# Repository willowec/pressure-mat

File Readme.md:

# Pressure Mat Project

This git repository contains all the code developed for the Electrical and Computer Engineering Capstone project of Evan Desmond and Willow Cunningham at the University of Maine, Orono. 

## The Mat

The pressure sensing mat uses the intersections between rows and columns of copper tape separated by velostat to form resistive pressure sensors. The mat has 28 rows and 56 columns, for a total of 1568 sensors at a resolution of 1cm^2.

## The PCB

Schematics for the PCB are in ```/board_kicad``` A render of the pcb is shown below.

## The Code

Code for the project is split into two primary parts: embedded side and host side.

### Embedded Code

The code that the RPI Pico runs is in the ```/board_code``` directory. It is responsible for controlling the ADCs and shift registers on the PCB in order to read the pressure sensors in the mat, and transmitting the mat data over USB serial to the connected host computer.

### Host Code

The python program in ```/GUI```  is used to view data recorded and transmitted by the interface board.

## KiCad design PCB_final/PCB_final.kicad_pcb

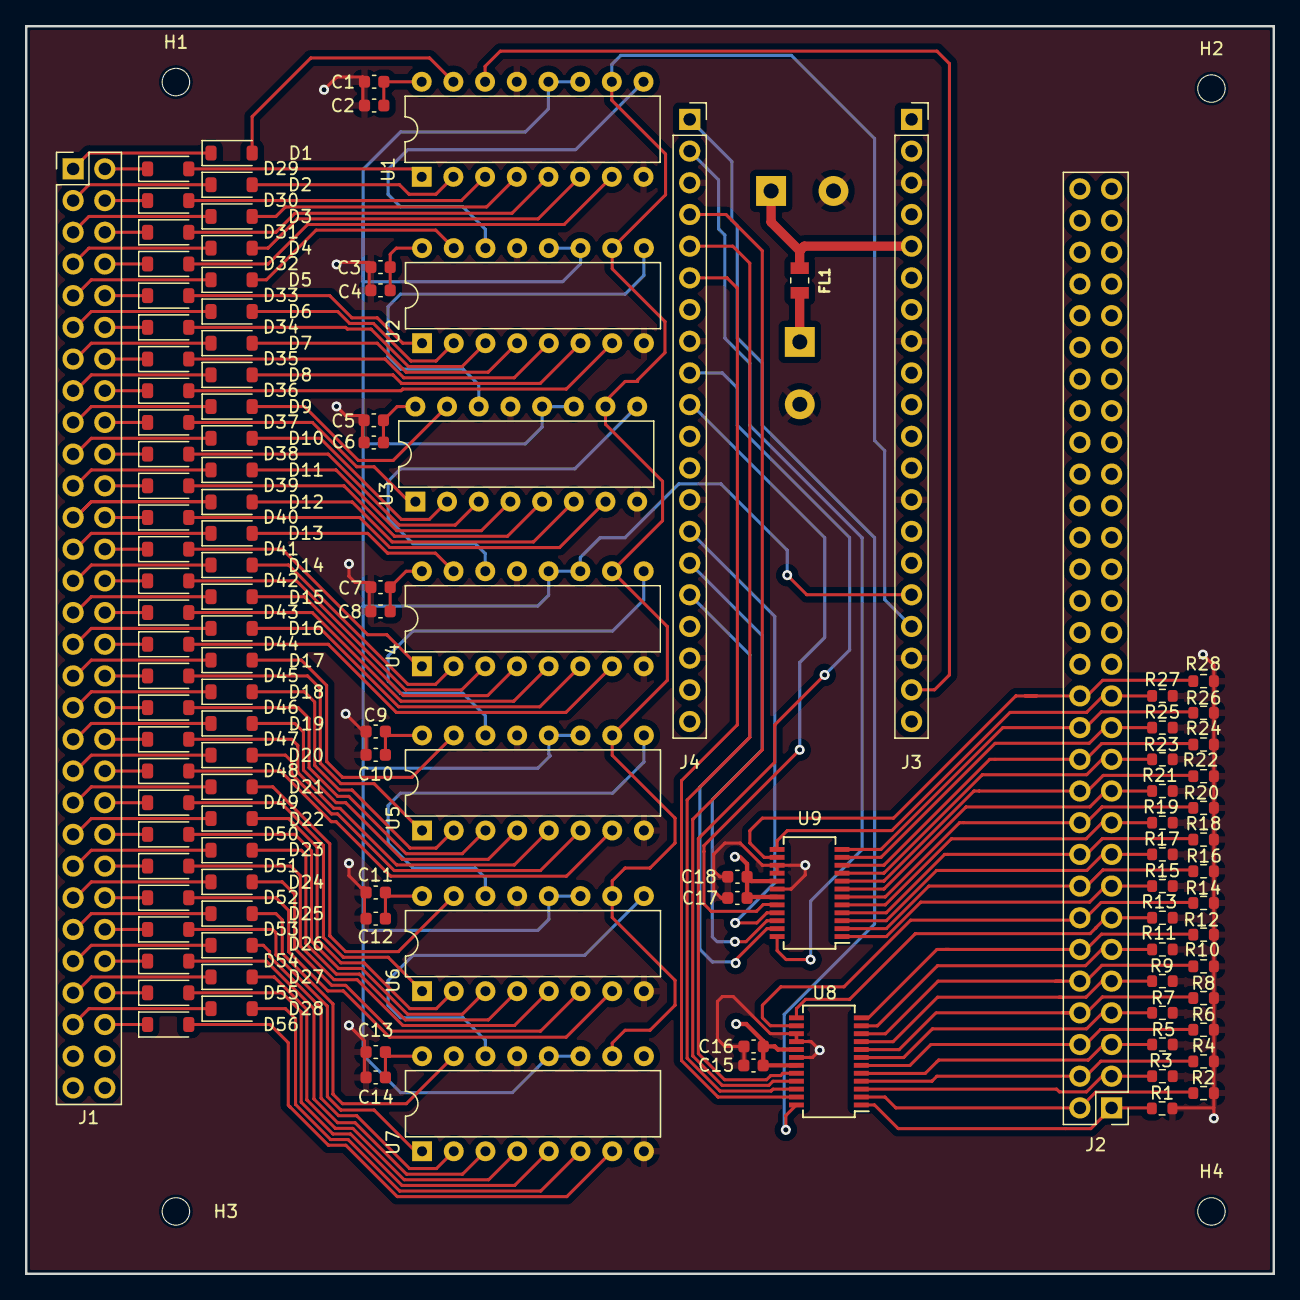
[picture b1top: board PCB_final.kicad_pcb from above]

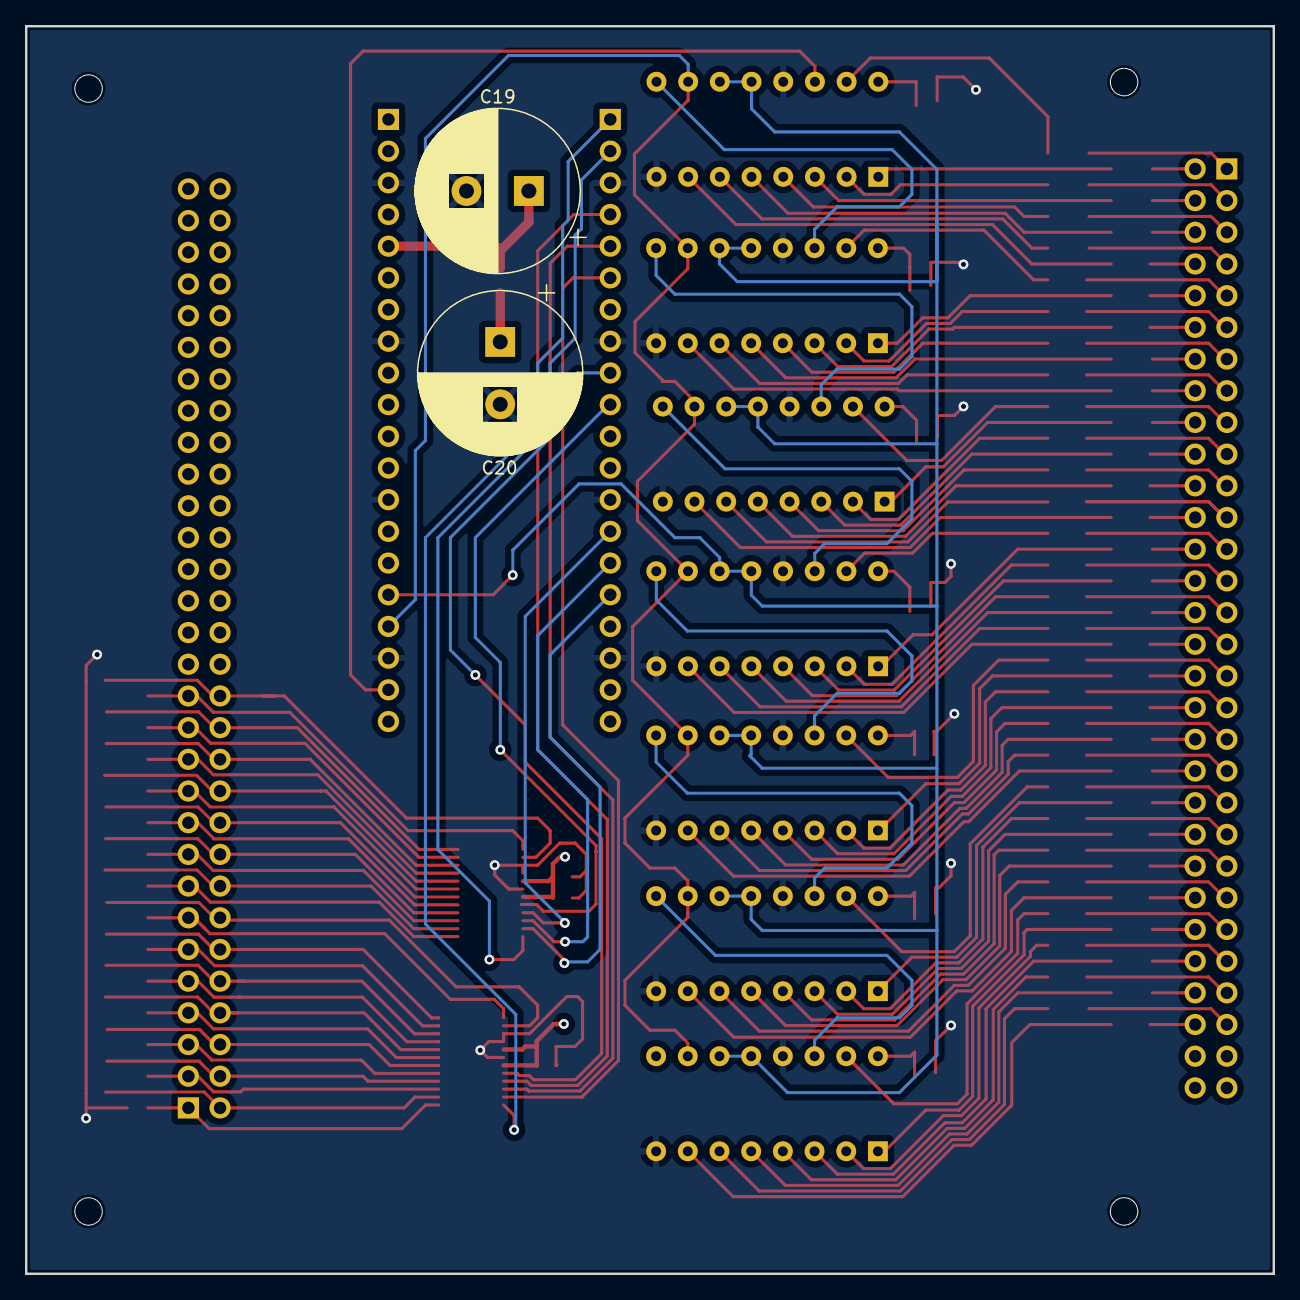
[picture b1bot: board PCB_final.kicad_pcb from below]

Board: 4 copper layers, 100.0 x 100.0 mm, 122 parts (2 on the bottom side), 162 nets.

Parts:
C1, C3, C5, C7, C9, C11, C13: 1uF; C_0603_1608Metric
C2, C4, C6, C8, C10, C12, C14: 0.1uF; C_0603_1608Metric
C15, C16, C17, C18: .1uF; C_0603_1608Metric
C19, C20: 4.7mF; CP_Radial_D13.0mm_P5.00mm
D1, D2, D3, D4, D5, D6, D7, D8, D9, D10, D11, D12, D13, D14, D15, D16, D17, D18, D19, D20, D21, D22, D23, D24, D25, D26, D27, D28, D29, D30, D31, D32, D33, D34, D35, D36, D37, D38, D39, D40, D41, D42, D43, D44, D45, D46, D47, D48, D49, D50, D51, D52, D53, D54, D55, D56: MMSD4148; D_SOD-123
FL1: BLM21BD272SN1L; BEADC2012X145N
H1, H2, H3, H4: MountingHole; MountingHole_2.2mm_M2
J1: 02x30_Shift_Register_Connector; PinHeader_2x30_P2.54mm_Vertical
J2: 02x30_ADC_Connector; PinHeader_2x30_P2.54mm_Vertical
J3: PicoPinSocketB; PinSocket_1x20_P2.54mm_Vertical
J4: PicoPinSocketA; PinSocket_1x20_P2.54mm_Vertical
R1, R2, R3, R4, R5, R6, R7, R8, R9, R10, R11, R12, R13, R14, R15, R16, R17, R18, R19, R20, R21, R22, R23, R24, R25, R26, R27, R28: 100k; R_0603_1608Metric
U1, U2, U3, U4, U5, U6, U7: 74HC595; DIP-16_W7.62mm
U8, U9: MAX11643EEG; SSOP-24_3.9x8.7mm_P0.635mm

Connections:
3V3_Pico: C19.1, FL1.1, J3.5
+3V3: C1.1, C2.1, C3.1, C4.1, C5.1, C6.1, C7.1, C8.1, C9.1, C10.1, C11.1, C12.1, C13.1, C14.1, C15.1, C16.1, C17.1, C18.1, C20.1, FL1.2, U1.16 (VCC), U2.16 (VCC), U3.16 (VCC), U4.16 (VCC), U5.16 (VCC), U6.16 (VCC), U7.16 (VCC), U8.17 (REF), U8.19 (VDD), U9.17 (REF), U9.19 (VDD)
/Interface Board/ADC1_EOC: J4.1, U8.24 (EOC)
/Interface Board/ADC2_EOC: J4.2, U9.24 (EOC)
/Interface Board/ADC_IN1: J2.1, R1.1, U8.1 (AIN0)
/Interface Board/ADC_IN2: J2.2, R2.1, U8.2 (AIN1)
/Interface Board/ADC_IN3: J2.3, R3.1, U8.3 (AIN2)
/Interface Board/ADC_IN4: J2.4, R4.1, U8.4 (AIN3)
/Interface Board/ADC_IN5: J2.5, R5.1, U8.5 (AIN4)
/Interface Board/ADC_IN6: J2.6, R6.1, U8.6 (AIN5)
/Interface Board/ADC_IN7: J2.7, R7.1, U8.7 (AIN6)
/Interface Board/ADC_IN8: J2.8, R8.1, U8.8 (AIN7)
/Interface Board/ADC_IN9: J2.9, R9.1, U8.9 (AIN8)
/Interface Board/ADC_IN10: J2.10, R10.1, U8.10 (AIN9)
/Interface Board/ADC_IN11: J2.11, R11.1, U8.11 (AIN10)
/Interface Board/ADC_IN12: J2.12, R12.1, U8.12 (AIN11)
/Interface Board/ADC_IN13: J2.13, R13.1, U8.13 (AIN12)
/Interface Board/ADC_IN14: J2.14, R14.1, U8.14 (AIN13)
/Interface Board/ADC_IN15: J2.15, R15.1, U9.1 (AIN0)
/Interface Board/ADC_IN16: J2.16, R16.1, U9.2 (AIN1)
/Interface Board/ADC_IN17: J2.17, R17.1, U9.3 (AIN2)
/Interface Board/ADC_IN18: J2.18, R18.1, U9.4 (AIN3)
/Interface Board/ADC_IN19: J2.19, R19.1, U9.5 (AIN4)
/Interface Board/ADC_IN20: J2.20, R20.1, U9.6 (AIN5)
/Interface Board/ADC_IN21: J2.21, R21.1, U9.7 (AIN6)
/Interface Board/ADC_IN22: J2.22, R22.1, U9.8 (AIN7)
/Interface Board/ADC_IN23: J2.23, R23.1, U9.9 (AIN8)
/Interface Board/ADC_IN24: J2.24, R24.1, U9.10 (AIN9)
/Interface Board/ADC_IN25: J2.25, R25.1, U9.11 (AIN10)
/Interface Board/ADC_IN26: J2.26, R26.1, U9.12 (AIN11)
/Interface Board/ADC_IN27: J2.27, R27.1, U9.13 (AIN12)
/Interface Board/ADC_IN28: J2.28, R28.1, U9.14 (AIN13)
/Interface Board/CS0: J4.9, U8.20 (CS)
/Interface Board/CS1: J4.10, U9.20 (CS)
/Interface Board/SER5: U4.9 (QH'), U5.14 (SER)
/Interface Board/SH_CLK: J3.16, U1.11 (SRCLK), U1.12 (RCLK), U2.11 (SRCLK), U2.12 (RCLK), U3.11 (SRCLK), U3.12 (RCLK), U4.11 (SRCLK), U4.12 (RCLK), U5.11 (SRCLK), U5.12 (RCLK), U6.11 (SRCLK), U6.12 (RCLK), U7.11 (SRCLK), U7.12 (RCLK)
/Interface Board/SH_CLR: J3.17, U1.10 (~SRCLR), U2.10 (~SRCLR), U3.10 (~SRCLR), U4.10 (~SRCLR), U5.10 (~SRCLR), U6.10 (~SRCLR), U7.10 (~SRCLR)
/Interface Board/SH_SERIN: J3.19, U1.14 (SER)
/Interface Board/SOUT1: D1.2 (A), U1.15 (QA)
/Interface Board/SOUT2: D29.2 (A), U1.1 (QB)
/Interface Board/SOUT3: D2.2 (A), U1.2 (QC)
/Interface Board/SOUT4: D30.2 (A), U1.3 (QD)
/Interface Board/SOUT5: D3.2 (A), U1.4 (QE)
/Interface Board/SOUT6: D31.2 (A), U1.5 (QF)
/Interface Board/SOUT7: D4.2 (A), U1.6 (QG)
/Interface Board/SOUT8: D32.2 (A), U1.7 (QH)
/Interface Board/SOUT9: D5.2 (A), U2.15 (QA)
/Interface Board/SOUT10: D33.2 (A), U2.1 (QB)
/Interface Board/SOUT11: D6.2 (A), U2.2 (QC)
/Interface Board/SOUT12: D34.2 (A), U2.3 (QD)
/Interface Board/SOUT13: D7.2 (A), U2.4 (QE)
/Interface Board/SOUT14: D35.2 (A), U2.5 (QF)
/Interface Board/SOUT15: D8.2 (A), U2.6 (QG)
/Interface Board/SOUT16: D36.2 (A), U2.7 (QH)
/Interface Board/SOUT17: D9.2 (A), U3.15 (QA)
/Interface Board/SOUT18: D37.2 (A), U3.1 (QB)
/Interface Board/SOUT19: D10.2 (A), U3.2 (QC)
/Interface Board/SOUT20: D38.2 (A), U3.3 (QD)
/Interface Board/SOUT21: D11.2 (A), U3.4 (QE)
/Interface Board/SOUT22: D39.2 (A), U3.5 (QF)
/Interface Board/SOUT23: D12.2 (A), U3.6 (QG)
/Interface Board/SOUT24: D40.2 (A), U3.7 (QH)
/Interface Board/SOUT25: D13.2 (A), U4.15 (QA)
/Interface Board/SOUT26: D41.2 (A), U4.1 (QB)
/Interface Board/SOUT27: D14.2 (A), U4.2 (QC)
/Interface Board/SOUT28: D42.2 (A), U4.3 (QD)
/Interface Board/SOUT29: D15.2 (A), U4.4 (QE)
/Interface Board/SOUT30: D43.2 (A), U4.5 (QF)
/Interface Board/SOUT31: D16.2 (A), U4.6 (QG)
/Interface Board/SOUT32: D44.2 (A), U4.7 (QH)
/Interface Board/SOUT33: D17.2 (A), U5.15 (QA)
/Interface Board/SOUT34: D45.2 (A), U5.1 (QB)
/Interface Board/SOUT35: D18.2 (A), U5.2 (QC)
/Interface Board/SOUT36: D46.2 (A), U5.3 (QD)
/Interface Board/SOUT37: D19.2 (A), U5.4 (QE)
/Interface Board/SOUT38: D47.2 (A), U5.5 (QF)
/Interface Board/SOUT39: D20.2 (A), U5.6 (QG)
/Interface Board/SOUT40: D48.2 (A), U5.7 (QH)
/Interface Board/SOUT41: D21.2 (A), U6.15 (QA)
/Interface Board/SOUT42: D49.2 (A), U6.1 (QB)
/Interface Board/SOUT43: D22.2 (A), U6.2 (QC)
/Interface Board/SOUT44: D50.2 (A), U6.3 (QD)
/Interface Board/SOUT45: D23.2 (A), U6.4 (QE)
/Interface Board/SOUT46: D51.2 (A), U6.5 (QF)
/Interface Board/SOUT47: D24.2 (A), U6.6 (QG)
/Interface Board/SOUT48: D52.2 (A), U6.7 (QH)
/Interface Board/SOUT49: D25.2 (A), U7.15 (QA)
/Interface Board/SOUT50: D53.2 (A), U7.1 (QB)
/Interface Board/SOUT51: D26.2 (A), U7.2 (QC)
/Interface Board/SOUT52: D54.2 (A), U7.3 (QD)
/Interface Board/SOUT53: D27.2 (A), U7.4 (QE)
/Interface Board/SOUT54: D55.2 (A), U7.5 (QF)
/Interface Board/SOUT55: D28.2 (A), U7.6 (QG)
/Interface Board/SOUT56: D56.2 (A), U7.7 (QH)
/Interface Board/SPI0_RX: J4.6, U8.23 (DOUT)
/Interface Board/SPI0_SCK: J4.4, U8.21 (SCLK)
/Interface Board/SPI0_TX: J4.5, U8.22 (DIN)
/Interface Board/SPI1_RX: J4.16, U9.23 (DOUT)
/Interface Board/SPI1_SCK: J4.14, U9.21 (SCLK)
/Interface Board/SPI1_TX: J4.15, U9.22 (DIN)
GND: C1.2, C2.2, C3.2, C4.2, C5.2, C6.2, C7.2, C8.2, C9.2, C10.2, C11.2, C12.2, C13.2, C14.2, C15.2, C16.2, C17.2, C18.2, C19.2, C20.2, J3.3, J3.8, J3.13, J3.18, J4.3, J4.8, J4.13, J4.18, R1.2, R2.2, R3.2, R4.2, R5.2, R6.2, R7.2, R8.2, R9.2, R10.2, R11.2, R12.2, R13.2, R14.2, R15.2, R16.2, R17.2, R18.2, R19.2, R20.2, R21.2, R22.2, R23.2, R24.2, R25.2, R26.2, R27.2, R28.2, U1.8 (GND), U1.13 (~OE), U2.8 (GND), U2.13 (~OE), U3.8 (GND), U3.13 (~OE), U4.8 (GND), U4.13 (~OE), U5.8 (GND), U5.13 (~OE), U6.8 (GND), U6.13 (~OE), U7.8 (GND), U7.13 (~OE), U8.15 (AIN14), U8.16 (AIN15), U8.18 (GND), U9.15 (AIN14), U9.16 (AIN15), U9.18 (GND)
unnamed: D1.1 (K), J1.1
unnamed: D2.1 (K), J1.3
unnamed: D3.1 (K), J1.5
unnamed: D4.1 (K), J1.7
unnamed: D5.1 (K), J1.9
unnamed: D6.1 (K), J1.11
unnamed: D7.1 (K), J1.13
unnamed: D8.1 (K), J1.15
unnamed: D9.1 (K), J1.17
unnamed: D10.1 (K), J1.19
unnamed: D11.1 (K), J1.21
unnamed: D12.1 (K), J1.23
unnamed: D13.1 (K), J1.25
unnamed: D14.1 (K), J1.27
unnamed: D15.1 (K), J1.29
unnamed: D16.1 (K), J1.31
unnamed: D17.1 (K), J1.33
unnamed: D18.1 (K), J1.35
unnamed: D19.1 (K), J1.37
unnamed: D20.1 (K), J1.39
unnamed: D21.1 (K), J1.41
unnamed: D22.1 (K), J1.43
unnamed: D23.1 (K), J1.45
unnamed: D24.1 (K), J1.47
unnamed: D25.1 (K), J1.49
unnamed: D26.1 (K), J1.51
unnamed: D27.1 (K), J1.53
unnamed: D28.1 (K), J1.55
unnamed: D29.1 (K), J1.2
unnamed: D30.1 (K), J1.4
unnamed: D31.1 (K), J1.6
unnamed: D32.1 (K), J1.8
unnamed: D33.1 (K), J1.10
unnamed: D34.1 (K), J1.12
unnamed: D35.1 (K), J1.14
unnamed: D36.1 (K), J1.16
unnamed: D37.1 (K), J1.18
unnamed: D38.1 (K), J1.20
unnamed: D39.1 (K), J1.22
unnamed: D40.1 (K), J1.24
unnamed: D41.1 (K), J1.26
unnamed: D42.1 (K), J1.28
unnamed: D43.1 (K), J1.30
unnamed: D44.1 (K), J1.32
unnamed: D45.1 (K), J1.34
unnamed: D46.1 (K), J1.36
unnamed: D47.1 (K), J1.38
unnamed: D48.1 (K), J1.40
unnamed: D49.1 (K), J1.42
unnamed: D50.1 (K), J1.44
unnamed: D51.1 (K), J1.46
unnamed: D52.1 (K), J1.48
unnamed: D53.1 (K), J1.50
unnamed: D54.1 (K), J1.52
unnamed: D55.1 (K), J1.54
unnamed: D56.1 (K), J1.56
unnamed: U1.9 (QH'), U2.14 (SER)
unnamed: U2.9 (QH'), U3.14 (SER)
unnamed: U3.9 (QH'), U4.14 (SER)
unnamed: U5.9 (QH'), U6.14 (SER)
unnamed: U6.9 (QH'), U7.14 (SER)

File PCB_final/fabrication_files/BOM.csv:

"Id";"Designator";"Footprint";"Quantity";"Designation";"Supplier and ref";
1;"C8,C14,C10,C2,C17,C4,C12,C6";"C_0603_1608Metric";8;"0.1uF";;;
2;"D35,D36,D2,D54,D18,D45,D25,D15,D11,D31,D55,D10,D30,D43,D56,D19,D9,D8,D44,D42,D32,D5,D28,D47,D6,D14,D21,D34,D52,D53,D3,D22,D17,D4,D40,D46,D29,D26,D48,D41,D49,D12,D37,D38,D23,D20,D7,D39,D51,D13,D27,D16,D33,D50,D24,D1";"D_SOD-123";56;"MMSD4148";;;
3;"R3,R13,R18,R27,R20,R25,R9,R26,R24,R11,R4,R14,R28,R2,R21,R10,R12,R5,R7,R17,R16,R23,R1,R8,R19,R15,R29,R22,R6";"R_0603_1608Metric";29;"100k";;;
4;"C9,C7,C5,C3,C11,C13,C1";"C_0603_1608Metric";7;"1uF";;;
5;"U2,U6,U3,U7,U4,U1,U5";"DIP-16_W7.62mm";7;"74HC595";;;
6;"J5";"PinSocket_1x20_P2.54mm_Vertical";1;"PicoPinSocketB";;;
7;"C16,C15";"C_0603_1608Metric";2;".1uF";;;
8;"J1";"PinHeader_2x30_P2.54mm_Vertical";1;"02x30_Shift_Register_Connector";;;
9;"U9,U8";"SSOP-24_3.9x8.7mm_P0.635mm";2;"MAX11643EEG";;;
10;"J2";"PinHeader_2x30_P2.54mm_Vertical";1;"02x30_ADC_Connector";;;
11;"U10";"SOT-23-5";1;"LM321";;;
12;"J6";"PinSocket_1x20_P2.54mm_Vertical";1;"PicoPinSocketA";;;

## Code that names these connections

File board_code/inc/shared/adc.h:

/*
Header file responsible for communicating via spi to the two ADC's of the project
This code is written assuming that the ADC's are MAX11643 chips
*/
#ifndef ADC_HEADER
#define ADC_HEADER

#include <stdint.h>
#include <stdbool.h>

#include "hardware/spi.h"

#define ADC_RESPONSE_LENGTH 28
#define CHANNELS_PER_ADC    14  // 14 pins of the adc's each are connected to the mat

#define SPI0_SCK_PIN        2
#define SPI0_TX_PIN         3
#define SPI0_RX_PIN         4

#define SPI1_SCK_PIN        10
#define SPI1_TX_PIN         11
#define SPI1_RX_PIN         12

#define SPI_CLOCKSPEED      2000000 // 2MHz
#define CS_SELECT           0
#define CS_DESELECT         1

#define ADC1_EOC_PIN        0
#define ADC2_EOC_PIN        1
#define ADC1_CS_PIN         6
#define ADC2_CS_PIN         7


struct adc_inst {
    uint8_t cs_pin;
    uint8_t eoc_pin;
    spi_inst_t *spi_channel;
};

/*
Initializes the spi channel used to talk to the ADCs, and calls initialze_adc() for both of them
Set dual_channel=true if using on board version 2 in order for each adc to have its own SPI channel
*/
void initialize_adcs(struct adc_inst *adc1, struct adc_inst *adc2, bool dual_channel);

/*
Initializes an ADC (sets setup register values, etc)
*/
void initialize_adc(struct adc_inst *adc);

/*
Gets samples from channel 0 to CHANNELS_PER_ADC of the adc_inst 'adc' and writes their values to 'out_vals'
*/
void get_adc_values(struct adc_inst* adc, uint8_t *out_vals);

/*
Wraps spi_write_blocking to communcicate with an adc
*/
void adc_write_blocking(struct adc_inst* adc, uint8_t *src, size_t len);

/*
Wraps spi_read_blocking to communcicate with an adc
*/
void adc_read_blocking(struct adc_inst* adc, uint8_t repeated_tx_data, uint8_t *dst, size_t len);

/*
Takes the raw response to a conversion request from the ADC and cleans it up to be a simple array of readings
*/
void cleanup_adc_response(uint8_t *resp, uint8_t *out_values);

#endif

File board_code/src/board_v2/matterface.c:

/*
Mat interface code for V2 of the PMI software
*/

#include <stdio.h>
#include <stdbool.h>

#include "hardware/gpio.h"
#include "pico/stdlib.h"

#include "matterface.h"
#include "transmitter.h"

#define LED_PIN         25

// For the interrupt-based mat read to work, some global variables are required
queue_t *mat_queue_ptr;
uint8_t row_data[ROW_WIDTH] = {9};  // intialize the row data with a clearly invalid data
struct queueItem row_item;

int column;
struct adc_inst *adc1_instance;
struct adc_inst *adc2_instance;
bool waiting_for_adc1;
bool waiting_for_adc2;
volatile bool reading_mat;  // must be volatile for global changes to be recognized


void initialize_shreg_pins()
{
    gpio_init(SH_CLK_PIN);
    gpio_set_dir(SH_CLK_PIN, GPIO_OUT);

    gpio_init(SH_CLR_PIN);
    gpio_set_dir(SH_CLR_PIN, GPIO_OUT);

    gpio_init(SH_SERIN_PIN);
    gpio_set_dir(SH_SERIN_PIN, GPIO_OUT);

    gpio_init(SH_SEROUT_PIN);
    gpio_set_dir(SH_SEROUT_PIN, GPIO_IN);

    // make sure the shift registers are initialized to zero
    clear_shreg();
}

void shift_shreg(int inval)
{
    // write the serial input value to the shift registers
    gpio_put(SH_SERIN_PIN, inval);

    // clock the shift registers once
    gpio_put(SH_CLK_PIN, 1);
    busy_wait_us_32(SHREG_GPIO_SLEEP_US);
    gpio_put(SH_CLK_PIN, 0);
}

void clear_shreg()
{
    // flicker the clear pin to reset the shift registers
    gpio_put(SH_CLR_PIN, 0);
    busy_wait_us_32(SHREG_GPIO_SLEEP_US);
    gpio_put(SH_CLR_PIN, 1);
}

/*
Callback function that is triggered by either of the ADC's EOC pins going low.
*/
void EOC_callback(uint gpio, uint32_t events) 
{
    if (!reading_mat) {
        return;   // do not process events if not reading the mat
    } 

    /* 
     * An EOC pin just went low! Let's handle this
     * 1. for the EOC pin:
     *  1.1. read results from the corresponding ADC
     *  1.2. transmit the results over the queue to core 1
     *  1.3. set waiting_for_adcX to false
     * 2. if waiting_for_adc1 and waiting_for_adc2 are both false:
     *  2.1. shift the shregs
     *  2.2. inc the column counter
     *  2.3. request a new conversion from both ADCs
     */

    int i;
    bool ret;

    // define a temp array for storing and processing the values returned from the ADCs
    uint8_t *resp = (uint8_t *)malloc(ADC_RESPONSE_LENGTH);

    // step 1
    if (gpio == ADC1_EOC_PIN) {
        // handle ADC1 results
        waiting_for_adc1 = false;

        // read the conversion results
        adc_read_blocking(adc1_instance, 0, resp, ADC_RESPONSE_LENGTH);
        cleanup_adc_response(resp, row_data);
    }
    else if (gpio == ADC2_EOC_PIN) {
        // handle ADC2 results
        waiting_for_adc2 = false;

        // read the conversion results
        adc_read_blocking(adc2_instance, 0, resp, ADC_RESPONSE_LENGTH);
        cleanup_adc_response(resp, row_data + CHANNELS_PER_ADC);
    }

    // step 2
    if ((!waiting_for_adc1) && (!waiting_for_adc2)) {
        // Both adc's have been read! push the row data onto the queue
        row_item.row_data = row_data;

        queue_add_blocking(mat_queue_ptr, &row_item);

        // set up the shift registers for the next adc sample requests
        shift_shreg(0);
        column++;

        // if column == COL_HEIGHT, then we are finished and should requet any more readings
        if (column == COL_HEIGHT) {
            reading_mat = false;
        }
        else {
            // delay before the next set of ADC requests
            busy_wait_us_32(ADC_READ_SLEEP_US); // cannot call sleep_us within interrupt handlers, busy wait instead

            // request all channels from both ADCs
            waiting_for_adc1 = true;
            waiting_for_adc2 = true;
            uint8_t conv_req = 0b10000000 | ((CHANNELS_PER_ADC - 1) << 3);  // conversion request command
            adc_write_blocking(adc1_instance, &conv_req, 1);
            adc_write_blocking(adc2_instance, &conv_req, 1);
        }
    }

    free(resp);
}

void initialize_EOC_interrupts() 
{
    reading_mat = false;

    // set up both EOC pins to trigger a callback on the falling edge of the EOC lines (falling edge occurs when the ADC completes its read)   
    gpio_set_irq_enabled_with_callback(ADC1_EOC_PIN, GPIO_IRQ_EDGE_FALL, true, &EOC_callback);
    gpio_set_irq_enabled(ADC2_EOC_PIN, GPIO_IRQ_EDGE_FALL, true);
}

void read_mat(queue_t *mat_queue, struct adc_inst *adc1, struct adc_inst *adc2)
{
    // do not start reading the mat if a read is already happening
    if (reading_mat) return;

    // Throttle the mat reading rate based on the CMake build variable
    sleep_ms(THROTTLE_SLEEP_MS);

    // start with a one in the shregs
    shift_shreg(1); // shift in a one
    shift_shreg(0); // move the one to the output line

    // set up the global variables for interrupt handling
    mat_queue_ptr = mat_queue;
    adc1_instance = adc1;
    adc2_instance = adc2;
    
    waiting_for_adc1 = false;
    waiting_for_adc2 = false;

    column = 0;

    // indicate that a read is currently happening
    reading_mat = true;

    // send the first ADC read requests to get things started
    // write a conversion request in scan mode 00 for channels 0 -> (CHANNELS_PER_ADC - 1), for CHANNELS_PER_ADC total channels
    uint8_t conv_req = 0b10000000 | ((CHANNELS_PER_ADC - 1) << 3);
    adc_write_blocking(adc1_instance, &conv_req, 1);
    adc_write_blocking(adc2_instance, &conv_req, 1);

    // now just busy-wait until the mat is completely read.
    int i = 0;
    while(reading_mat) 
        i++;
    
    return;
}


void prettyprint_mat(uint8_t *mat)
{
    int i;
    for (i = 0; i < MAT_SIZE; i++)
    {
        if ((i % ROW_WIDTH) == 0) {
            printf("\b  \n");   // on every row, clear the trailing comma and add a newline
        }

        printf("%02x, ", mat[i]);
    }

    printf("\b  \n");
}

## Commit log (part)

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2023-05-16 Stopped tracking png
2023-05-17 Sampling code has artefacts alternating every read. investigationg
2023-05-25 minor tweaks
2023-05-28 Added note about the diodes
2023-08-30 Replaced incorrect alt text
2023-09-04 Added 4/7 shift registers and connected them to connection block, I believe this could be improved with bus lines
2023-09-05 Added 7/7 shift registers with fully connected inputs and outputs, need to look into necesity of decoupling capacitor on GND
2023-09-05 ignoring irrelevant kicad stuff
2023-09-05 removed irrelevant kicad stuff
2023-09-05 Changed all shift registers to be on the same SCLK, RCLK and OE. Also connected shift register 4 to 5 using node names
2023-09-06 used nodes to reconnect ADC's to new connectors and added voltage dividers to all ADC inputs
2023-09-06 added diodes to between all shift register outputs and the connector
2023-09-07 ignoring info cache
2023-09-07 added decouple caps for the ADCs
2023-09-11 Created new folder for PCB with RP2040 included
2023-09-11 Separated RP2040 and interface board components into multiple sheets
2023-09-12 changed diodes to the correct surface mount diodes we will be using on the final pcb
2023-09-12 beautified shift registers by putting decoupling capacitors as external elements and put in actual capacitor values
2023-09-15 Added guide for programming the pico
2023-09-16 ignoring builds
2023-09-16 began stub of python version of the dummy adc
2023-09-16 Added short explanation of the c_example
2023-09-16 began multicore/spi example
2023-09-17 Added C example of an spi client running on core 1 and an spi controller running on core 2, talking to each other
2023-09-17 typo fix
2023-09-17 Began C implementation
2023-09-18 issue seems to be fixed
2023-09-19 Moved old pcb to prototypes
2023-09-19 Added active-low pass filter for power supply to schematic. Need to decide which OP AMP, resistor, and capacitor to use.
2023-09-19 Added clock connection for ADCs
2023-09-19 Selected values for low-pass filter: C=0.1uF, R=500ohm, Fc=3.2kHz. Still need to select op amp, but we can probably go with whatever is readily available in parts cabinent
2023-09-19 noconnected relevant pins
2023-09-19 Added clock pin connections
2023-09-20 Updated op amp and added rpi pico to schematic
2023-09-21 Added load past session button
2023-09-21 Created a sessions folder in GUI to hold past sessions. Also added a folder of a 'past session' with 3 images to test GUI with
2023-09-21 Connected all pins to the pico
2023-09-22 Changed images to be 56 wide by 28 tall. Beautified GUI. And got image scaling to work so the foot pressure images are displayed at 10x
2023-09-22 Began embedded code
2023-09-25 Changed to use only one spi channe.
2023-09-25 Added file selector to 'load past session' button, does not properly update image yet
2023-09-25 'Load past session' button now updates image on page but is not scaled correctly yet
2023-09-25 began adc code
2023-09-26 Added spi wrapper functions to adc.h
2023-09-26 Added the get_next_img() function that will get an image with +/- 1 index to the current image. Applied this function to image navigator buttons to get them functioning. Still need to add protections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
2023-09-26 Added comments to get_next_image(), load_past_img_next(), and load_past_img_prev()
2023-09-26 Attempts to read from adc
2023-09-27 SPI comms with the fake adc's most of the way there, although the response is never being sent
2023-09-27 Added session class to be initialized when the start session button is clicked. Not tested yet and only creates a folder with the current date and time right now
2023-09-28 Added footprints to the ADCS
2023-09-28 upon initialization the session class now creates a folder named by the current date and time in the /sessions directory. folder name is in the format of yy_mm_dd_THH_MM_SS
2023-10-01 Added footprints to all components
2023-10-01 nearly finished with pcb routing
2023-10-02 fully connected, thermal pad errors
2023-10-02 fixed board edge
2023-10-02 Changed Reciever class so that connecting to the board is its own function. Modified the connect_board() function in the MainWindow class so that it updates the reciever with the input port and baud 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
2023-10-03 Started creating image saving to the correct index within the reciever class
2023-10-07 Began mat interface code. Code-side ADC issues are all fixed.
2023-10-08 Now interfacing and prettyprinting the mat
2023-10-08 Attempting to see difference between weighted and unweighted mat
2023-10-11 Added PWR and GND planes to PCB
2023-10-12 PCB complete and redesigned w 4 layers. Passes desgin rule checker except for most of the silk screens. Schematic updated to connect adc unused pins to ground and beatified schematic
2023-10-12 PCB silkscreen moved to stop warnings. Still getting a lot of seemingly unimportant errors from silkscreen. Updated design constraints to match manufacturer capabilities. Fixed a trace that was clipp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
2023-10-12 Created directory for PCB fabrication files and populated it
2023-10-13 Deleted manual PCB fab files and switched to JLCPCB plugin fab file output. Modified BOM and Positions files, removing the shift registers and pico pin headers. I suggest we also remove ribbon cable 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
2023-10-13 slight formatting
2023-10-15 Many caps on schematic were labeled c1 and c2 incorrectly. Swapped power supply filter to Pi filter, but with no value for L yet.
2023-10-15 Fixed tpe hinting issue that prevented startup
2023-10-15 Moved communcation with the mat to its own module. Many issues outstanding
2023-10-16 most basic possible transmitting
2023-10-16 Added MCP6001 PCB
2023-10-16 Board now waits for message to start sampling
2023-10-16 Found naming errors with schematic and a few traces in PCB that weren't connected correctly. PCB now passes DRC with only a few warnings about silkscreen
2023-10-16 Comms argely working. Issue where board fails early into first mat read
2023-10-17 Removed filter from schematic and PCB. Adjusted tracings on PCB and schematic for ADC inputs so that each ADC has 14 inputs
2023-10-17 Removed old PCB production files and added new ones. Removed components from BOM and positions files that we are soldering ourselves
2023-10-17 debugging in progress
2023-10-19 board communcations are still flawed. Current im_array conversion is correct. Need to investigate fwrite
2023-10-19 Chnaged comms to use hexadecimal. Issue now is that it seems to only be transmitting up a value 0-16
2023-10-19 prettyprinting the array shows that the problem might be with tthe saving of the image
2023-10-23 Fixed a lot of issues with the data transmission to the GUI, but data is still checkerboarded at source
2023-10-24 Finally figured out ADC comms once and for all
2023-10-24 Using new info, fixed comms
2023-10-24 ignoring oycache
2023-10-24 Updated filter's ferrite bead and capacitors on schematic and PCB. Power supply filter now fully integrated
2023-10-30 Added note on pcb to indicate direction pico faces
2023-10-30 Updated clock rate
2023-10-31 temp fix eliminating ADC1 due to hardware failure
2023-11-02 Initial structure layout
2023-11-03 A historical moment. Genuinely worked the first try
2023-11-07 Multicore example now includes built-in queue
2023-11-07 Updated kicad PCB to use both SPI channels of the RPI Pico
2023-11-07 Changed inductor silkscreen to meet production constraints
2023-11-07 Made matterface talk to both ADC's again
2023-11-07 Fixed issue where first column of mat would be skipped by shregs
2023-11-07 Moved conversion of mat reading from array to np.ndarray from save_image() to run()
2023-11-07 Began linking calibration logiv to GUI
2023-11-08 Updated PCB for quality of life. Increased size to 100mmx100mm. Rotated pico 180 degrees. Aligned ribbon cable connectors. Moved silk screens to better locations. Moved mounting holes to better locat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
2023-11-08 Restored normal functions, mat seems to be working after it got a good night's sleep?
2023-11-08 UI fully finished, actual curbe calculations needs a lot of work
2023-11-09 Ignoring calibrator unless it is calibrated
2023-11-09 Moved silkscreen text to better locations
2023-11-09 Added a test for extreme order polynomial
2023-11-09 Made calibration select a lower polyfit degree if not enough samples are passed
2023-11-14 changed sample rate to over 1Hz
2023-11-14 Added default calibration values. Calibrator is still not playing nice
2023-11-14 disabled saving of default cal
2023-11-14 Added data plotting file
2023-11-15 Now plotting calibration curves
2023-11-16 Calculating calibration curves via scipy semi-implemented
2023-11-16 ZERO CURVE FIT FAILURES!!!!!!!
2023-11-16 Added step size plot
2023-11-16 plot_readings now calculates percentage error at max step size
2023-11-17 Removed obsolete calibration buttons
2023-11-17 Removed outdated image code
2023-11-20 Added average cal curves
2023-11-20 Added % error calculations to the stats box
2023-11-21 Added slider to GUI. Removed nav buttons. Still need to flesh out slider
2023-11-27 minor edits
2023-11-27 Added a second build target for board v2 and a print_info command
2023-11-28 Started trying to use interrupts, but program unable to continue after finishing interrupt cycle
2023-11-28 Adding a print statement within the busy loop of read_mat airquotes fixed the issue. Need to find workaround
2023-11-28 Made reading_mat volatile to fix the issue. Duh...
2023-11-28 Current speed limit for sampling the mat is ~16Hz. Pretty gpod
2023-11-28 Removed erroneous print
2023-11-28 minor matterface changes
2023-11-28 Moved GUI out of prototypes folder. Added PCB production files for PCB V2
2023-11-28 Transmission has a flaw where it drops one reading after 9 or 10 reads
2023-11-28 Added debug capabilities to the GUI. It appears that the hardware stdio is timing out or something and transmitting when it shouldn't
2023-11-28 Added zeroing functionality to GUI. Not tested yet.
2023-11-29 Added experiment using putchar_raw() to skip conversion to headecimal
2023-11-29 Changed serial communications to transmit raw bytes isntead of hexadecimal characters
2023-11-30 Updated gui to work with raw bytes
2023-11-30 Added session stats display
2023-11-30 Added number of errors tracking
2023-12-01 Added a rate limited bild target for use with GUI
2023-12-01 Applied DC offset before calibration.
2023-12-01 Changed DC offsets to be passed into calibration curves and applied after calibration, then clipped at zero. Mat shows all black with zero weight on it!
2023-12-01 Moved get_mat_data and began calibrate_individual_sensor
2023-12-02 Saving individual cal curves
2023-12-02 removed unnecessary imports
2023-12-04 Minor docs improvements and added ability to get_mat_data to simply print the mat
2023-12-04 Added ability for individual calibrator to plot recorded data even if the curve fit fails
2023-12-05 Made calibration default to averaged curves
2023-12-05 Changing to account for area of sensor
2023-12-05 renamed raw data to have pressure for individual sensors instead of full mat
2023-12-05 Reworked cals to follow true Pa
2023-12-05 Fixed error calcs
2023-12-06 Added functionality to ignore datapoints over x-k for curve fitting and set that max to 200 for better R2 results
2023-12-06 Updated titles and revision dates on schematics
2023-12-07 Regenerated cal curves based on sensor area fix
2023-12-07 Updated kikad ignores
2023-12-07 Began updating readmes
2023-12-07 Renamed PCB_final to board
2023-12-07 Stopped tracking report.txt
2023-12-07 Moved symbol lib into board kicad folder
2023-12-07 symbol lib fixes
2023-12-07 removed outdated pytest
2023-12-07 Added python requirements
2023-12-07 removed old talk about the dummy max
2023-12-11 formatting improvements and rare division by zero fix
2023-12-11 Added usage information
2023-12-11 minor formatting changes
2023-12-11 Removed the C example taken from the rpi website
2023-12-11 Added a bit more info
2023-12-11 Added result
2023-12-11 Changed sleep order to be less confusing
2024-02-07 removed small area cal
2024-02-07 doc updates
2024-02-07 Updated readme's
